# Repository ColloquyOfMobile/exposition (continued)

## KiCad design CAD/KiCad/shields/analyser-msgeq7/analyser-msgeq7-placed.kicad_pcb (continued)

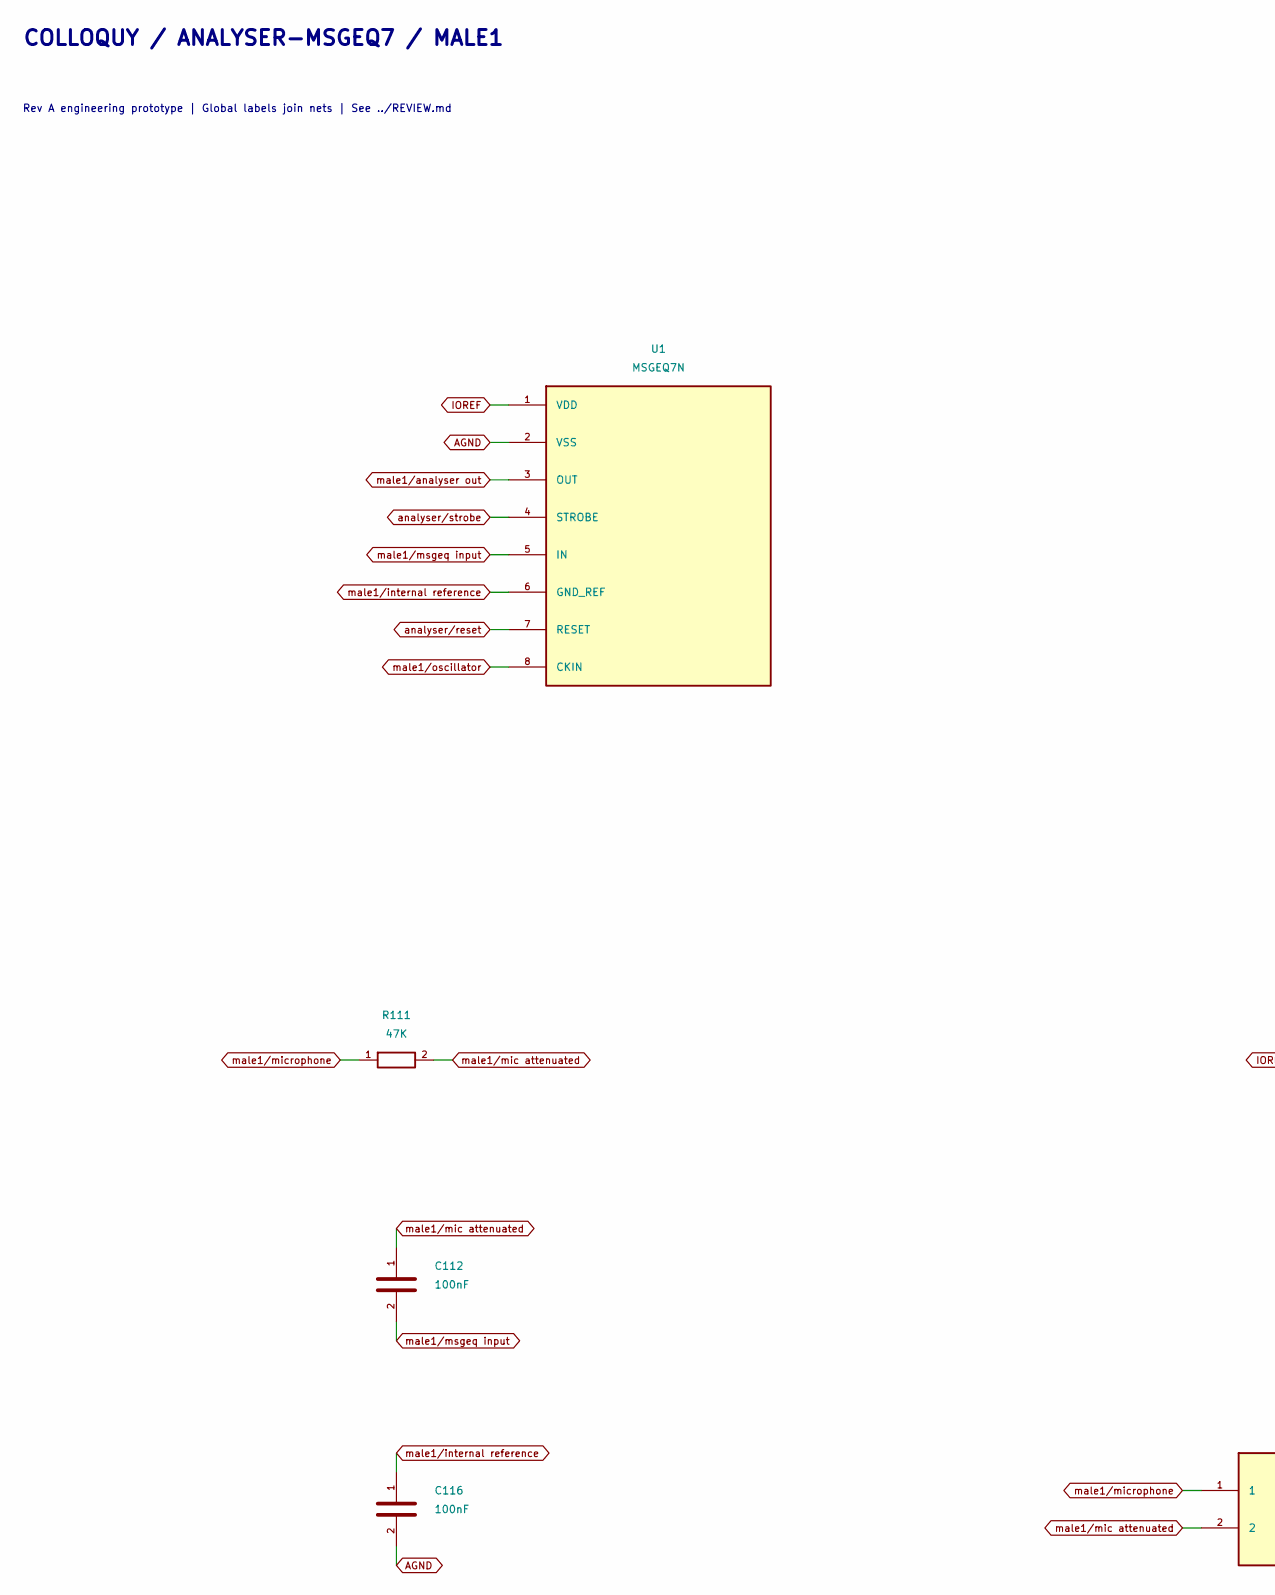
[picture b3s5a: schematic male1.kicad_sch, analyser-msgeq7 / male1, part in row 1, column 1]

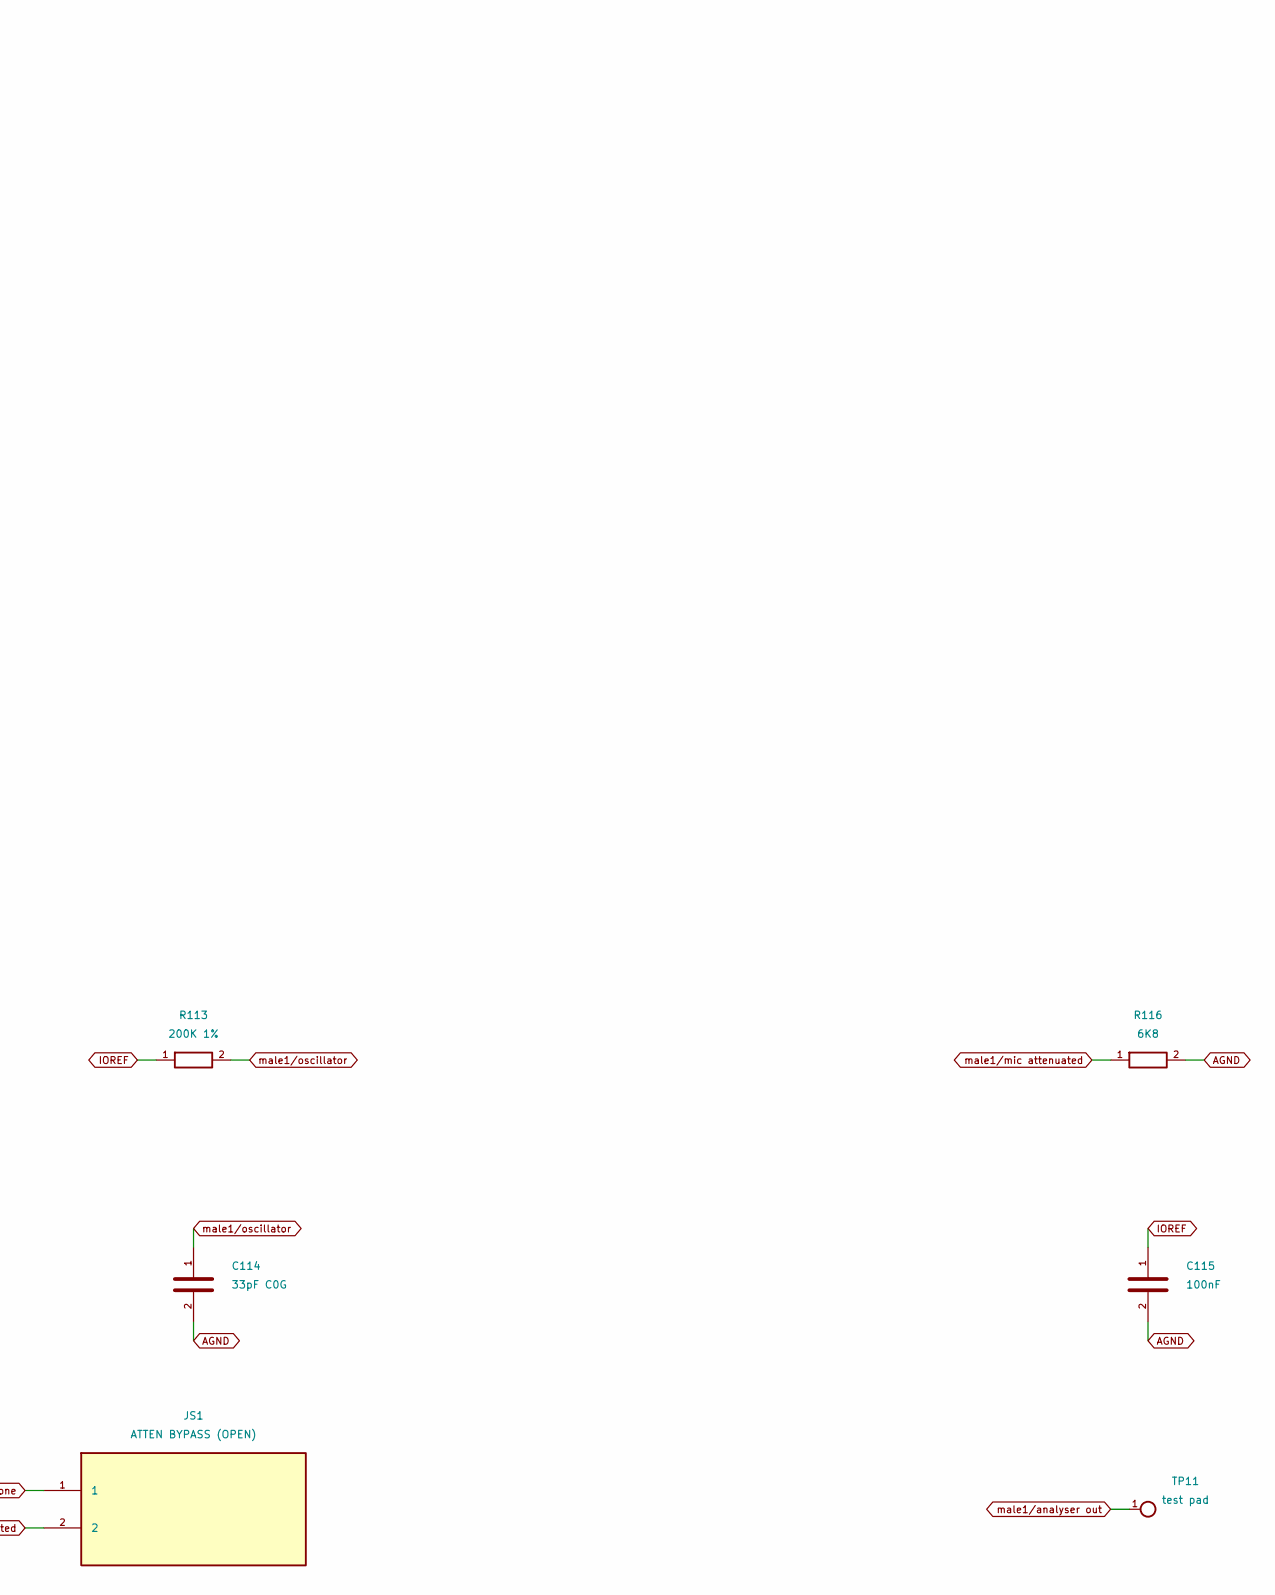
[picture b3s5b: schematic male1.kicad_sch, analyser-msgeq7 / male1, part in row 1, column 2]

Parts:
C112, C115, C116: 100nF; C_0603_1608Metric
C114: 33pF C0G; C_0603_1608Metric
JS1: ATTEN BYPASS (OPEN); SolderJumper-2_P1.3mm_Open_RoundedPad1.0x1.5mm
R111: 47K; R_0603_1608Metric
R113: 200K 1%; R_0603_1608Metric
R116: 6K8; R_0603_1608Metric
TP11: test pad; TestPoint_Pad_D1.5mm
U1: MSGEQ7N; SOIC-8_3.9x4.9mm_P1.27mm

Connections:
AGND: C114.2, C115.2, C116.2, R116.2, U1.2 (VSS); also elsewhere on the board
IOREF: C115.1, R113.1, U1.1 (VDD); also elsewhere on the board
analyser/reset: U1.7 (RESET); also elsewhere on the board
analyser/strobe: U1.4 (STROBE); also elsewhere on the board
male1/analyser out: TP11.1, U1.3 (OUT); also elsewhere on the board
male1/internal reference: C116.1, U1.6 (GND_REF)
male1/mic attenuated: C112.1, JS1.2, R111.2, R116.1
male1/microphone: JS1.1, R111.1; also elsewhere on the board
male1/msgeq input: C112.2, U1.5 (IN)
male1/oscillator: C114.1, R113.2, U1.8 (CKIN)

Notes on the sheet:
COLLOQUY / ANALYSER-MSGEQ7 / MALE1
Rev A engineering prototype | Global labels join nets | See ../REVIEW.md

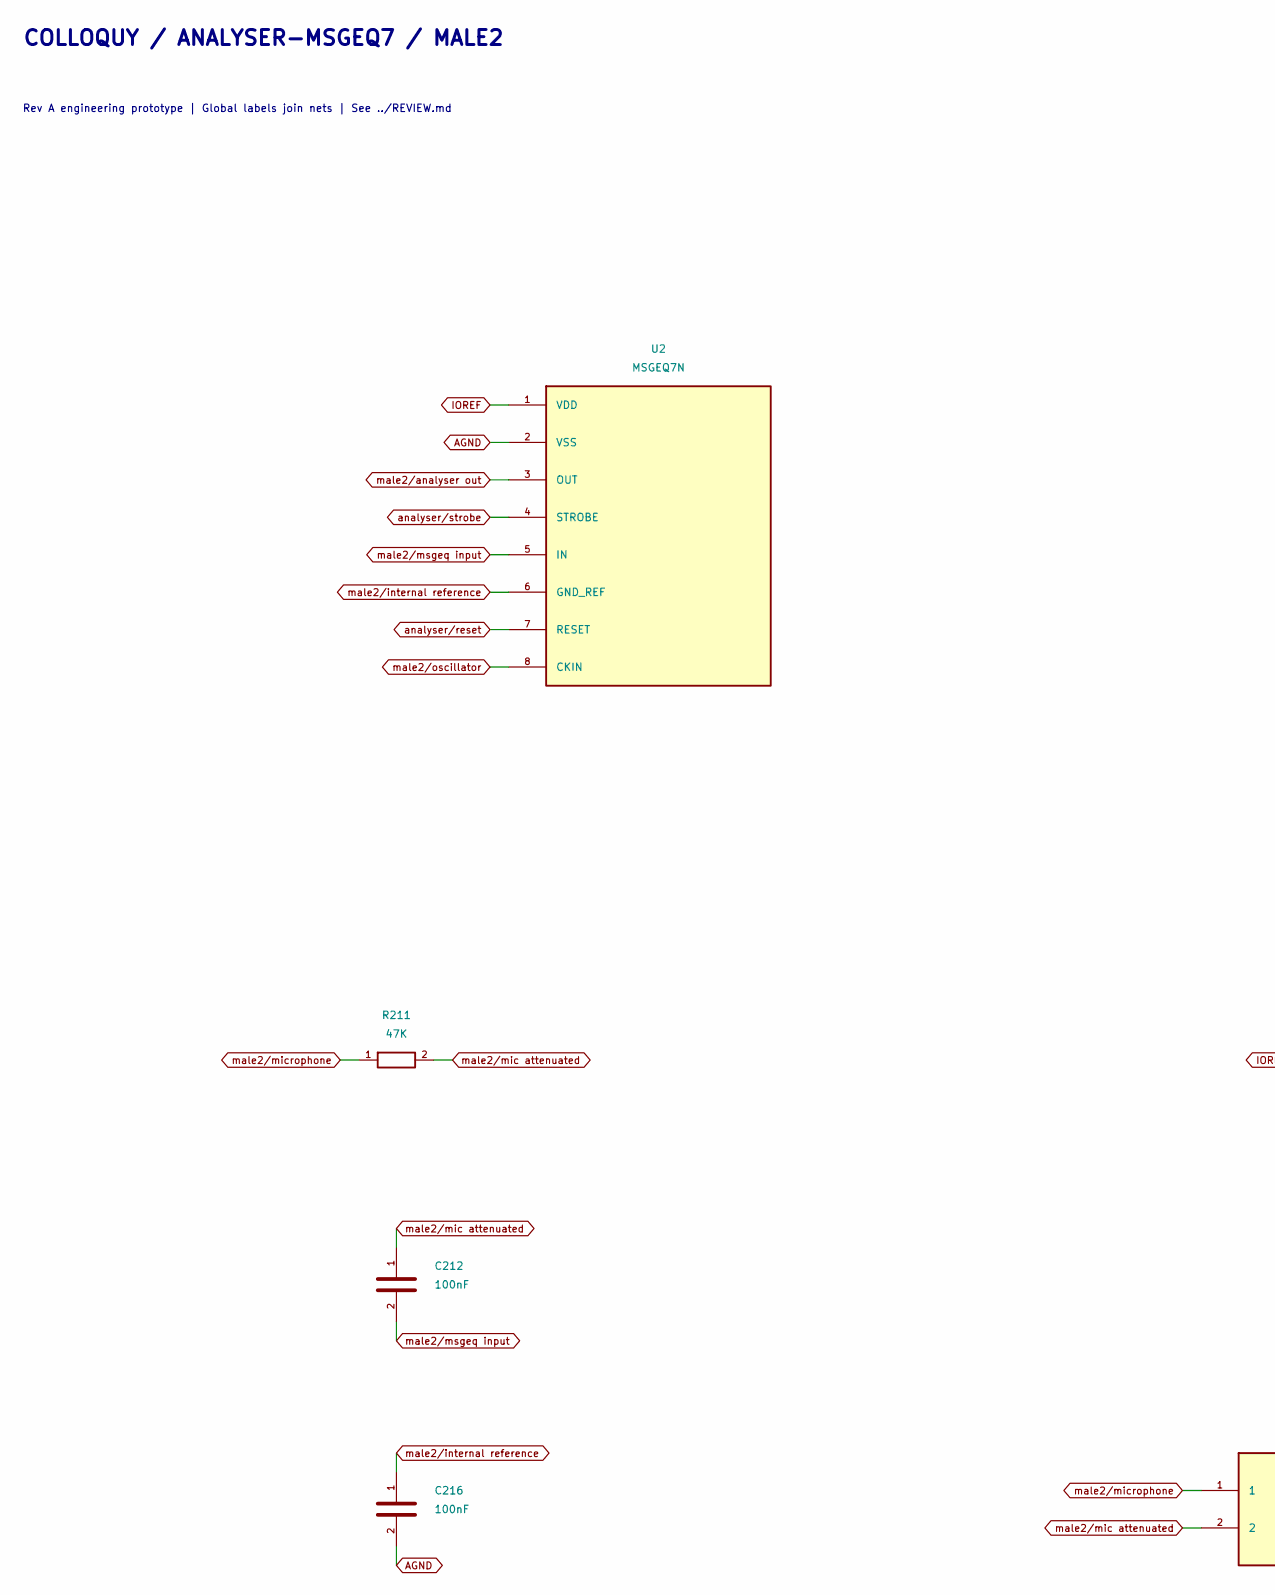
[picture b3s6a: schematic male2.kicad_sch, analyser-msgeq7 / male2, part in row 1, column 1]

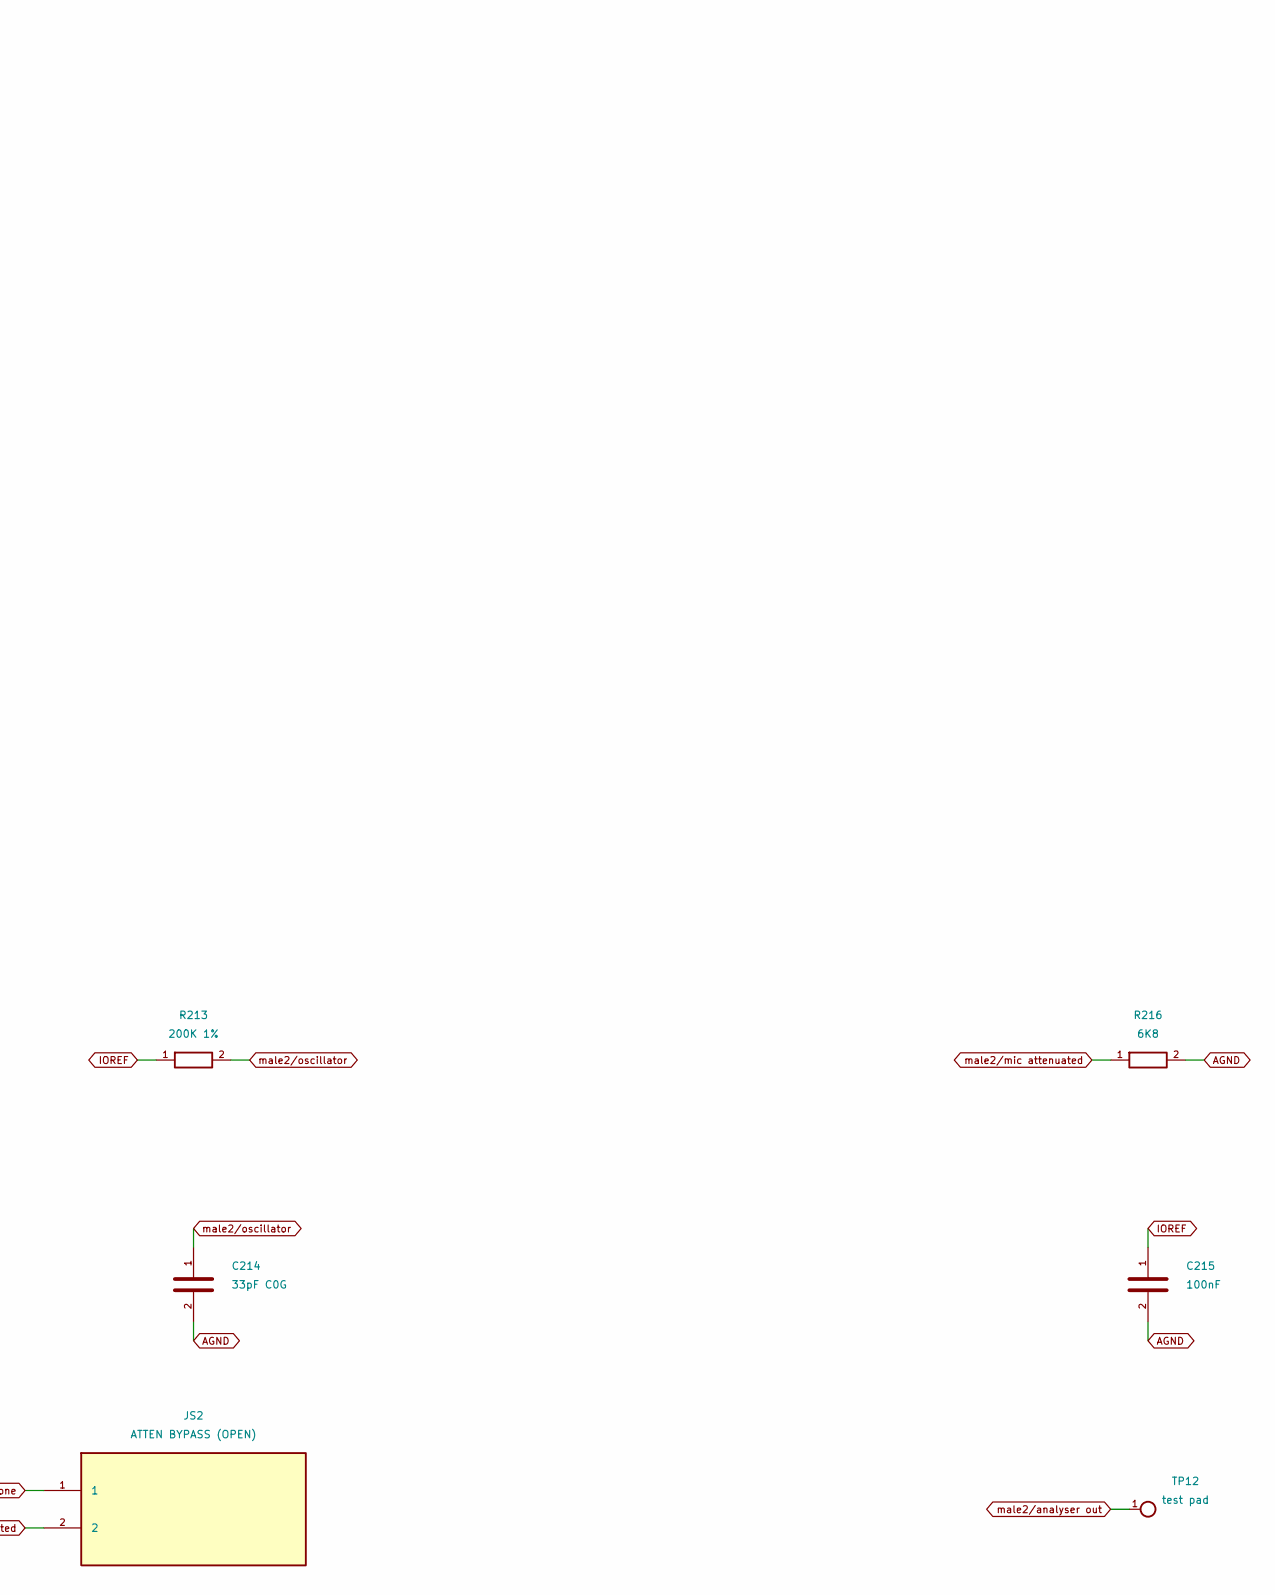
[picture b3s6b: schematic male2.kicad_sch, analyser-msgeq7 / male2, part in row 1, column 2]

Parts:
C212, C215, C216: 100nF; C_0603_1608Metric
C214: 33pF C0G; C_0603_1608Metric
JS2: ATTEN BYPASS (OPEN); SolderJumper-2_P1.3mm_Open_RoundedPad1.0x1.5mm
R211: 47K; R_0603_1608Metric
R213: 200K 1%; R_0603_1608Metric
R216: 6K8; R_0603_1608Metric
TP12: test pad; TestPoint_Pad_D1.5mm
U2: MSGEQ7N; SOIC-8_3.9x4.9mm_P1.27mm

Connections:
AGND: C214.2, C215.2, C216.2, R216.2, U2.2 (VSS); also elsewhere on the board
IOREF: C215.1, R213.1, U2.1 (VDD); also elsewhere on the board
analyser/reset: U2.7 (RESET); also elsewhere on the board
analyser/strobe: U2.4 (STROBE); also elsewhere on the board
male2/analyser out: TP12.1, U2.3 (OUT); also elsewhere on the board
male2/internal reference: C216.1, U2.6 (GND_REF)
male2/mic attenuated: C212.1, JS2.2, R211.2, R216.1
male2/microphone: JS2.1, R211.1; also elsewhere on the board
male2/msgeq input: C212.2, U2.5 (IN)
male2/oscillator: C214.1, R213.2, U2.8 (CKIN)

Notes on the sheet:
COLLOQUY / ANALYSER-MSGEQ7 / MALE2
Rev A engineering prototype | Global labels join nets | See ../REVIEW.md

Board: 2 copper layers, 57 parts (1 on the bottom side), 34 nets, no tracks yet.

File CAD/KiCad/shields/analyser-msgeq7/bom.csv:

Reference,Value,Footprint,MPN,Assembly
JA1,ANALYSER - KEY 22,Shields:Socket_2x11_Key22,,fit
U3,MSGEQ7N,Shields:SOIC-8_3.9x4.9mm_P1.27mm,MSGEQ7N,fit
R311,47K,Shields:R_0603_1608Metric,,fit
R313,200K 1%,Shields:R_0603_1608Metric,,fit
R316,6K8,Shields:R_0603_1608Metric,,fit
C312,100nF,Shields:C_0603_1608Metric,,fit
C314,33pF C0G,Shields:C_0603_1608Metric,,fit
C315,100nF,Shields:C_0603_1608Metric,,fit
C316,100nF,Shields:C_0603_1608Metric,,fit
U4,MSGEQ7N,Shields:SOIC-8_3.9x4.9mm_P1.27mm,MSGEQ7N,fit
R411,47K,Shields:R_0603_1608Metric,,fit
R413,200K 1%,Shields:R_0603_1608Metric,,fit
R416,6K8,Shields:R_0603_1608Metric,,fit
C412,100nF,Shields:C_0603_1608Metric,,fit
C414,33pF C0G,Shields:C_0603_1608Metric,,fit
C415,100nF,Shields:C_0603_1608Metric,,fit
C416,100nF,Shields:C_0603_1608Metric,,fit
U5,MSGEQ7N,Shields:SOIC-8_3.9x4.9mm_P1.27mm,MSGEQ7N,fit
R511,47K,Shields:R_0603_1608Metric,,fit
R513,200K 1%,Shields:R_0603_1608Metric,,fit
R516,6K8,Shields:R_0603_1608Metric,,fit
C512,100nF,Shields:C_0603_1608Metric,,fit
C514,33pF C0G,Shields:C_0603_1608Metric,,fit
C515,100nF,Shields:C_0603_1608Metric,,fit
C516,100nF,Shields:C_0603_1608Metric,,fit
U1,MSGEQ7N,Shields:SOIC-8_3.9x4.9mm_P1.27mm,MSGEQ7N,fit
R111,47K,Shields:R_0603_1608Metric,,fit
R113,200K 1%,Shields:R_0603_1608Metric,,fit
R116,6K8,Shields:R_0603_1608Metric,,fit
C112,100nF,Shields:C_0603_1608Metric,,fit
C114,33pF C0G,Shields:C_0603_1608Metric,,fit
C115,100nF,Shields:C_0603_1608Metric,,fit
C116,100nF,Shields:C_0603_1608Metric,,fit
U2,MSGEQ7N,Shields:SOIC-8_3.9x4.9mm_P1.27mm,MSGEQ7N,fit
R211,47K,Shields:R_0603_1608Metric,,fit
R213,200K 1%,Shields:R_0603_1608Metric,,fit
R216,6K8,Shields:R_0603_1608Metric,,fit
C212,100nF,Shields:C_0603_1608Metric,,fit
C214,33pF C0G,Shields:C_0603_1608Metric,,fit
C215,100nF,Shields:C_0603_1608Metric,,fit
C216,100nF,Shields:C_0603_1608Metric,,fit

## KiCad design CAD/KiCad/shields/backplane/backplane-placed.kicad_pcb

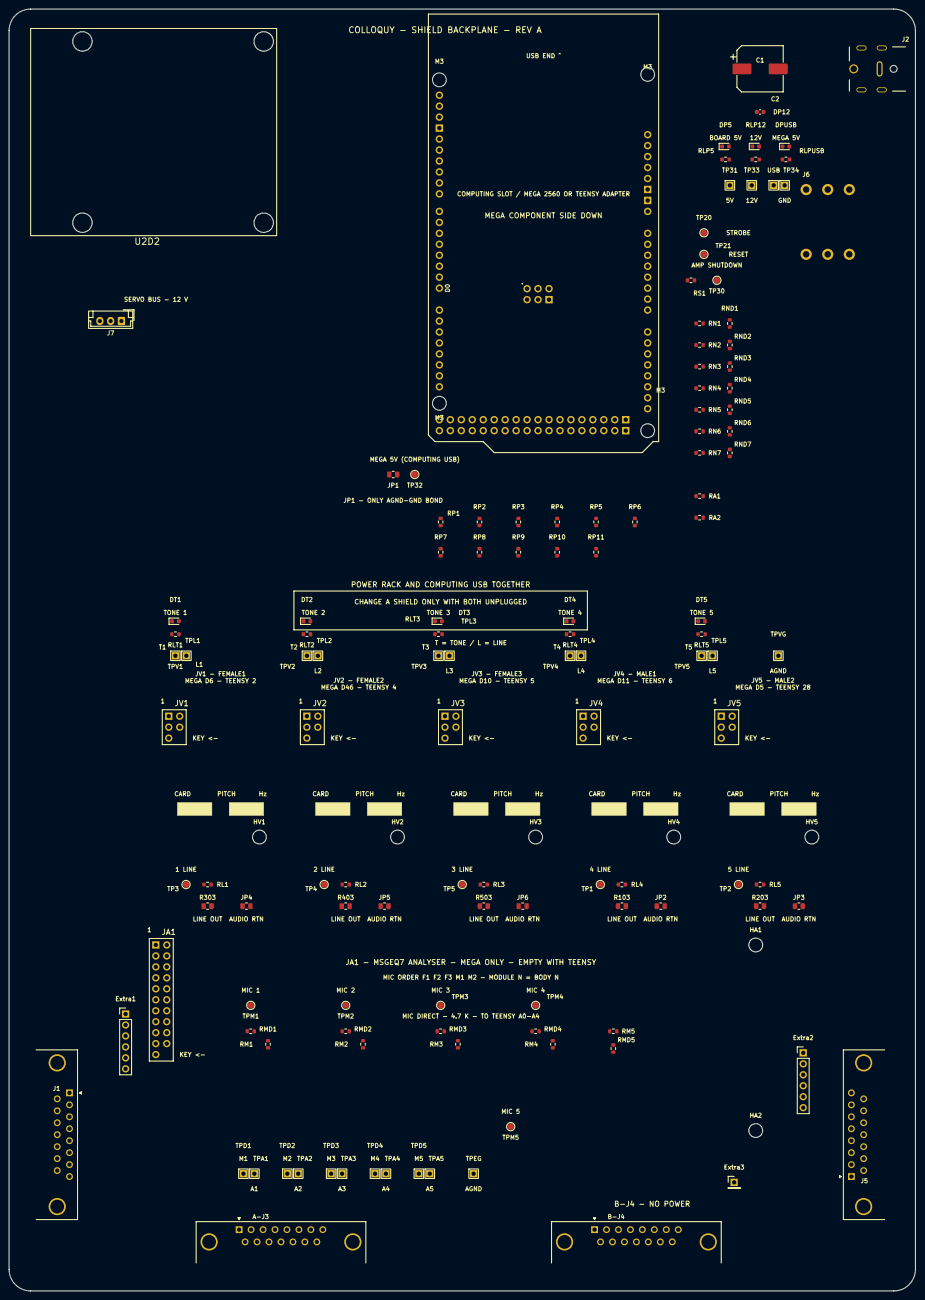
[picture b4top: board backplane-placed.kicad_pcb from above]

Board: 4 copper layers, 210.0 x 297.0 mm, 141 parts (0 on the bottom side), 94 nets, no tracks yet.

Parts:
A1: Arduino Mega 2560; Mega_Front_Mirrored
A-J3: DSUB-15; DSUB-15_Pins_Horizontal_P2.77x2.84mm_EdgePinOffset4.94mm_Ho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
B-J4: DSUB-15; DSUB-15_Pins_Horizontal_P2.77x2.84mm_EdgePinOffset4.94mm_Ho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
C1: 470uF 25V; CP_Elec_10x10.5
C2: 100nF; C_0603_1608Metric
DP5, DP12: GREEN LED; LED_0603_1608Metric
DPUSB: GREEN LED; LED_0603_1608Metric
DT1, DT2, DT3, DT4, DT5: YELLOW LED; LED_0603_1608Metric
Extra1, Extra2: 1x6 header; PinHeader_1x06_P2.54mm_Vertical
Extra3: 1x1 pad; PinHeader_1x01_P2.54mm_Vertical
HA1, HA2: M3 analyser retention; MountingHole_3.2mm_M3
HM1, HM2, HM3, HM4: M3; front spacer OD <=4mm; screw head on rear; MountingHole_3.2mm_M3_SlimFront
HV1, HV2, HV3, HV4, HV5: M3 card retention; MountingHole_3.2mm_M3
J1, J5: DSUB-15; DSUB-15_Pins_Horizontal_P2.77x2.84mm_EdgePinOffset4.94mm_Ho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
J2: DC jack; PJ-082BH_jack_10A
J6: screw bridge; screw_brigde
J7: JST EH 3; JST_EH_B3B-EH-A_1x03_P2.50mm_Vertical
JA1: ANALYSER - KEY 22; Header_2x11_Key22
JP1, JP2, JP3, JP4, JP5, JP6: 0R; R_0805_2012Metric
JV1: female1 - KEY 6; Header_2x03_Key6
JV2: female2 - KEY 6; Header_2x03_Key6
JV3: female3 - KEY 6; Header_2x03_Key6
JV4: male1 - KEY 6; Header_2x03_Key6
JV5: male2 - KEY 6; Header_2x03_Key6
M1: U2D2; u2d2_mounting
R103, R203, R303, R403, R503: 100R; R_0805_2012Metric
RA1, RA2: 330R; R_0603_1608Metric
RL1, RL2, RL3, RL4, RL5: 100K; R_0603_1608Metric
RLP5: 2K2; R_0603_1608Metric
RLP12: 4K7; R_0603_1608Metric
RLPUSB: 2K2; R_0603_1608Metric
RLT1, RLT2, RLT3, RLT4, RLT5: 1K5; R_0603_1608Metric
RM1, RM2, RM3, RM4, RM5: 4K7; R_0603_1608Metric
RMD1, RMD2, RMD3, RMD4, RMD5: 1M; R_0603_1608Metric
RN1, RN2, RN3, RN4, RN5, RN6, RN7: 330R; R_0603_1608Metric
RND1, RND2, RND3, RND4, RND5, RND6, RND7: 100K; R_0603_1608Metric
RP1, RP2, RP3, RP4, RP5, RP6, RP7, RP8, RP9, RP10, RP11: 10K provisional; R_0603_1608Metric
RS1: 10K; R_0603_1608Metric
TP1: male1/filter out; TestPoint_Pad_D1.5mm
TP2: male2/filter out; TestPoint_Pad_D1.5mm
TP3: female1/filter out; TestPoint_Pad_D1.5mm
TP4: female2/filter out; TestPoint_Pad_D1.5mm
TP5: female3/filter out; TestPoint_Pad_D1.5mm
TP20: analyser/strobe; TestPoint_Pad_D1.5mm
TP21: analyser/reset; TestPoint_Pad_D1.5mm
TP30: amp shutdown; TestPoint_Pad_D1.5mm
TP31: +5V; TestPin_1x01_P2.54mm
TP32: MEGA_5V; TestPoint_Pad_D1.5mm
TP33: +12V; TestPin_1x01_P2.54mm
TP34: GND; TestPin_1x01_P2.54mm
TPA1: female1/analyser out; TestPin_1x01_P2.54mm
TPA2: female2/analyser out; TestPin_1x01_P2.54mm
TPA3: female3/analyser out; TestPin_1x01_P2.54mm
TPA4: male1/analyser out; TestPin_1x01_P2.54mm
TPA5: male2/analyser out; TestPin_1x01_P2.54mm
TPD1: female1/mic direct; TestPin_1x01_P2.54mm
TPD2: female2/mic direct; TestPin_1x01_P2.54mm
TPD3: female3/mic direct; TestPin_1x01_P2.54mm
TPD4: male1/mic direct; TestPin_1x01_P2.54mm
TPD5: male2/mic direct; TestPin_1x01_P2.54mm
TPEG: AGND; TestPin_1x01_P2.54mm
TPL1: female1/filter out; TestPin_1x01_P2.54mm
TPL2: female2/filter out; TestPin_1x01_P2.54mm
TPL3: female3/filter out; TestPin_1x01_P2.54mm
TPL4: male1/filter out; TestPin_1x01_P2.54mm
TPL5: male2/filter out; TestPin_1x01_P2.54mm
TPM1: female1/microphone; TestPoint_Pad_D1.5mm
TPM2: female2/microphone; TestPoint_Pad_D1.5mm
TPM3: female3/microphone; TestPoint_Pad_D1.5mm
TPM4: male1/microphone; TestPoint_Pad_D1.5mm
TPM5: male2/microphone; TestPoint_Pad_D1.5mm
TPUSB: MEGA_5V; TestPin_1x01_P2.54mm
TPV1: female1/tone; TestPin_1x01_P2.54mm
TPV2: female2/tone; TestPin_1x01_P2.54mm
TPV3: female3/tone; TestPin_1x01_P2.54mm
TPV4: male1/tone; TestPin_1x01_P2.54mm
TPV5: male2/tone; TestPin_1x01_P2.54mm
TPVG: AGND; TestPin_1x01_P2.54mm

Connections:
+5V: A-J3.9, C1.1, C2.1, J1.15, J2.1, J5.15, J6.3, J6.5, J6.6, JV1.5, JV2.5, JV3.5, JV4.5, JV5.5, RLP5.1, TP31.1
+12V: A-J3.2, J1.7, J5.7, J7.2, RLP12.1, TP33.1
AGND: JA1.2, JA1.4, JA1.6, JA1.8, JA1.10, JA1.16, JP1.1, JP2.2, JP3.2, JP4.2, JP5.2, JP6.2, JV1.4, JV2.4, JV3.4, JV4.4, JV5.4, RL1.2, RL2.2, RL3.2, RL4.2, RL5.2, RMD1.2, RMD2.2, RMD3.2, RMD4.2, RMD5.2, RP1.2, RP2.2, RP3.2, RP4.2, RP5.2, RP6.2, RP7.2, RP8.2, RP9.2, RP10.2, RP11.2, TPEG.1, TPVG.1
GND: A1.GND1, A1.GND2, A1.GND3, A1.GND4, A1.GND5, A1.GND6, A-J3.0, A-J3.1, B-J4.0, C1.2, C2.2, DP5.1, DP12.1, DPUSB.1, DT1.1, DT2.1, DT3.1, DT4.1, DT5.1, J1.0, J1.8, J2.2, J5.0, J5.8, J6.1, J6.2, J6.4, J7.1, JA1.20, JA1.21, JP1.2, JV1.2, JV2.2, JV3.2, JV4.2, JV5.2, RND1.2, RND2.2, RND3.2, RND4.2, RND5.2, RND6.2, RND7.2, TP34.1
MEGA_5V: A1.5V1, A1.5V2, A1.5V3, A1.5V4, JA1.19, RLPUSB.1, RS1.2, TP32.1, TPUSB.1
amp shutdown: A1.D2, RS1.1, TP30.1
analyser/reset: A1.D3, JA1.18, TP21.1
analyser/strobe: A1.D4, JA1.17, TP20.1
centre/spare1: B-J4.7, Extra3.1
dxl_data: A-J3.10, J1.14, J5.14, J7.3
female1/analyser out: A1.A0, JA1.11, TPA1.1
female1/audio return: J5.4, JP4.1
female1/filter out: JV1.3, R303.1, RL1.1, TP3.1, TPL1.1
female1/line out: J5.12, R303.2
female1/mic direct: A1.D26, RM1.2, RMD1.1, TPD1.1
female1/microphone: J5.6, JA1.1, RM1.1, TPM1.1
female1/neopixel: J5.13, RN1.2
female1/neopixel/driven: A1.D14, RN1.1, RND1.1
female1/photosensor: A1.A5, J5.5, RP1.1
female1/spare1: Extra2.1, J5.1
female1/spare2: Extra2.2, J5.2
female1/spare3: Extra2.3, J5.3
female1/spare4: Extra2.4, J5.9
female1/spare5: Extra2.5, J5.10
female1/spare6: Extra2.6, J5.11
female1/tone: A1.D6, JV1.1, RLT1.1, TPV1.1
female2/analyser out: A1.A1, JA1.12, TPA2.1
female2/audio return: J1.4, JP5.1
female2/filter out: JV2.3, R403.1, RL2.1, TP4.1, TPL2.1
female2/line out: J1.12, R403.2
female2/mic direct: A1.D27, RM2.2, RMD2.1, TPD2.1
female2/microphone: J1.6, JA1.3, RM2.1, TPM2.1
female2/neopixel: J1.13, RN2.2
female2/neopixel/driven: A1.D7, RN2.1, RND2.1
female2/photosensor: A1.A6, J1.5, RP2.1
female2/spare1: Extra1.1, J1.1
female2/spare2: Extra1.2, J1.2
female2/spare3: Extra1.3, J1.3
female2/spare4: Extra1.4, J1.9
female2/spare5: Extra1.5, J1.10
female2/spare6: Extra1.6, J1.11
female2/tone: A1.D46, JV2.1, RLT2.1, TPV2.1
female3/analyser out: A1.A2, JA1.13, TPA3.1
female3/audio return: A-J3.5, JP6.1
female3/filter out: JV3.3, R503.1, RL3.1, TP5.1, TPL3.1
female3/line out: A-J3.12, R503.2
female3/mic direct: A1.D28, RM3.2, RMD3.1, TPD3.1
female3/microphone: A-J3.3, JA1.5, RM3.1, TPM3.1
female3/neopixel: A-J3.11, RN3.2
female3/neopixel/driven: A1.D8, RN3.1, RND3.1
female3/photosensor: A1.A7, A-J3.4, RP3.1
female3/tone: A1.D10, JV3.1, RLT3.1, TPV3.1
led/DP5: DP5.2, RLP5.2
led/DP12: DP12.2, RLP12.2
led/DPUSB: DPUSB.2, RLPUSB.2
led/DT1: DT1.2, RLT1.2
led/DT2: DT2.2, RLT2.2
led/DT3: DT3.2, RLT3.2
led/DT4: DT4.2, RLT4.2
led/DT5: DT5.2, RLT5.2
male1/analyser out: A1.A3, JA1.14, TPA4.1
male1/audio return: B-J4.2, JP2.1
male1/aux: B-J4.1, RA1.2
male1/aux driven: A1.D24, RA1.1
male1/bar neopixel: B-J4.15, RN6.2
male1/bar neopixel/driven: A1.D16, RN6.1, RND6.1
male1/filter out: JV4.3, R103.1, RL4.1, TP1.1, TPL4.1
male1/line out: B-J4.9, R103.2
male1/mic direct: A1.D29, RM4.2, RMD4.1, TPD4.1
male1/microphone: A-J3.13, JA1.7, RM4.1, TPM4.1
male1/neopixel: A-J3.6, RN4.2
male1/neopixel/driven: A1.D9, RN4.1, RND4.1
male1/photosensor/A: A1.A8, A-J3.14, RP4.1
male1/photosensor/B: A1.A9, A-J3.7, RP5.1
male1/photosensor/C: A1.A10, A-J3.15, RP6.1
male1/photosensor/D: A1.A11, A-J3.8, RP7.1
male1/tone: A1.D11, JV4.1, RLT4.1, TPV4.1
male2/analyser out: A1.A4, JA1.15, TPA5.1
male2/audio return: B-J4.14, JP3.1
male2/aux: B-J4.13, RA2.2
male2/aux driven: A1.D25, RA2.1
male2/bar neopixel: B-J4.8, RN7.2
male2/bar neopixel/driven: A1.D17, RN7.1, RND7.1
male2/filter out: JV5.3, R203.1, RL5.1, TP2.1, TPL5.1
male2/line out: B-J4.6, R203.2
male2/mic direct: A1.D30, RM5.2, RMD5.1, TPD5.1
male2/microphone: B-J4.10, JA1.9, RM5.1, TPM5.1
male2/neopixel: B-J4.3, RN5.2
male2/neopixel/driven: A1.D15, RN5.1, RND5.1
male2/photosensor/A: A1.A12, B-J4.11, RP8.1
male2/photosensor/B: A1.A13, B-J4.4, RP9.1
male2/photosensor/C: A1.A14, B-J4.12, RP10.1
male2/photosensor/D: A1.A15, B-J4.5, RP11.1
male2/tone: A1.D5, JV5.1, RLT5.1, TPV5.1
